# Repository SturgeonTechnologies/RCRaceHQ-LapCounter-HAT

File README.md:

# RC Race HQ Lap Counter HAT

Open hardware for the [RC Race HQ](https://www.rcracehq.com) lap counter: a
Raspberry Pi 4 HAT that sits between the track's timing loop and the RTL-SDR.

| Path | What | Status |
|---|---|---|
| [`burst-detector-hat/`](burst-detector-hat) | v0: splitter + AD8307 log detector + LM393 burst flag + ADS1115 signal strength. KiCad project, gerbers, JLCPCB BOM/CPL | Fab files done, board not built or tested yet |
| [`breadboard-v1.md`](breadboard-v1.md) | v1 loop front end (LMH6624 amp + detector) as a breadboard build: parts checklist, ASCII schematic, hole-by-hole steps | Not built or tested yet |

Transponder IDs come from the RTL-SDR through
[OpenStint](https://github.com/zsellera/openstint). The HAT tells the Pi
*when* a transponder is over the loop and how strong it is. Without a HAT, the
loop coax goes straight into the RTL-SDR, which is how the lap counter runs
today.

Software and Pi setup:
[RCRaceHQ-LapCounter-Install](https://github.com/SturgeonTechnologies/RCRaceHQ-LapCounter-Install)
and [RCRaceHQ-LapCounter-App](https://github.com/SturgeonTechnologies/RCRaceHQ-LapCounter-App).

## Buy or build

Anyone may build this board. Assembled, tested boards will be available from
RC Race HQ.

## License

[CERN-OHL-S-2.0](LICENSE). You may build, modify and sell boards made from
this design. If you ship a modified board, you must publish your modified
design files under the same licence. See [NOTICE](NOTICE). "RC Race HQ" is a
trademark of Sturgeon Technologies LLC and isn't covered by the licence.

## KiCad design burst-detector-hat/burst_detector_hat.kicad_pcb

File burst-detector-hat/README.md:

# Burst-detector HAT (lap counter v0 front end)

Raspberry Pi 4 HAT (65 × 56.5 mm, M2.5 holes on the HAT pattern) that sits
between the timing loop and the RTL-SDR.

```
loop -> balun -> J1 SMA -> TVS -> 3-way resistive splitter -+-> J2 SMA -> RTL-SDR (IDs, via OpenStint)
                                                           +-> 3-8 MHz bandpass -> AD8307 log detector
AD8307 RSSI (25 mV/dB) -+-> ADS1115 AIN0 (I2C 0x48, pins 3/5) -> signal strength
                        +-> LM393 vs RV1 threshold -> GPIO17 (pin 11) + BURST LED
```

It tells the Pi *when* a transponder is over the loop and how strong it is.
The ID still comes from the SDR. Power is the Pi's 5 V/3.3 V header pins, so
USB-C or a PoE HAT both work. J4 is an unconnected pass-through for the Pi's
2×2 PoE header, with a copper keep-out around it.

## Ordering (JLCPCB)
- Gerbers: `fab/burst_detector_hat_gerbers.zip` (2 layers, 1.6 mm, HASL).
- Assembly (top side): `fab/bom_jlcpcb.csv` + `fab/cpl_jlcpcb.csv`.
  Check every LCSC part number and the U1/U2/U3 pin-1 rotation in JLC's preview.
- Hand-solder: J3 2×20 stacking header, J4 2×2 stacking header (optional).

## Bring-up
1. Power from the Pi; LED off with no loop connected.
2. `i2cdetect -y 1` shows `48`.
3. Turn RV1 until the LED goes out with the loop empty, then back off a little.
4. Transponder on the loop: LED on, ~650 rising edges/s on GPIO17.

## Rebuild
`source ~/tools/kicad-env.sh && JAVA=... FREEROUTING=... tools/build.sh`
regenerates everything from `tools/design.py`, autoroutes, runs ERC/DRC
(`fab/reports/`) and rewrites `fab/`.

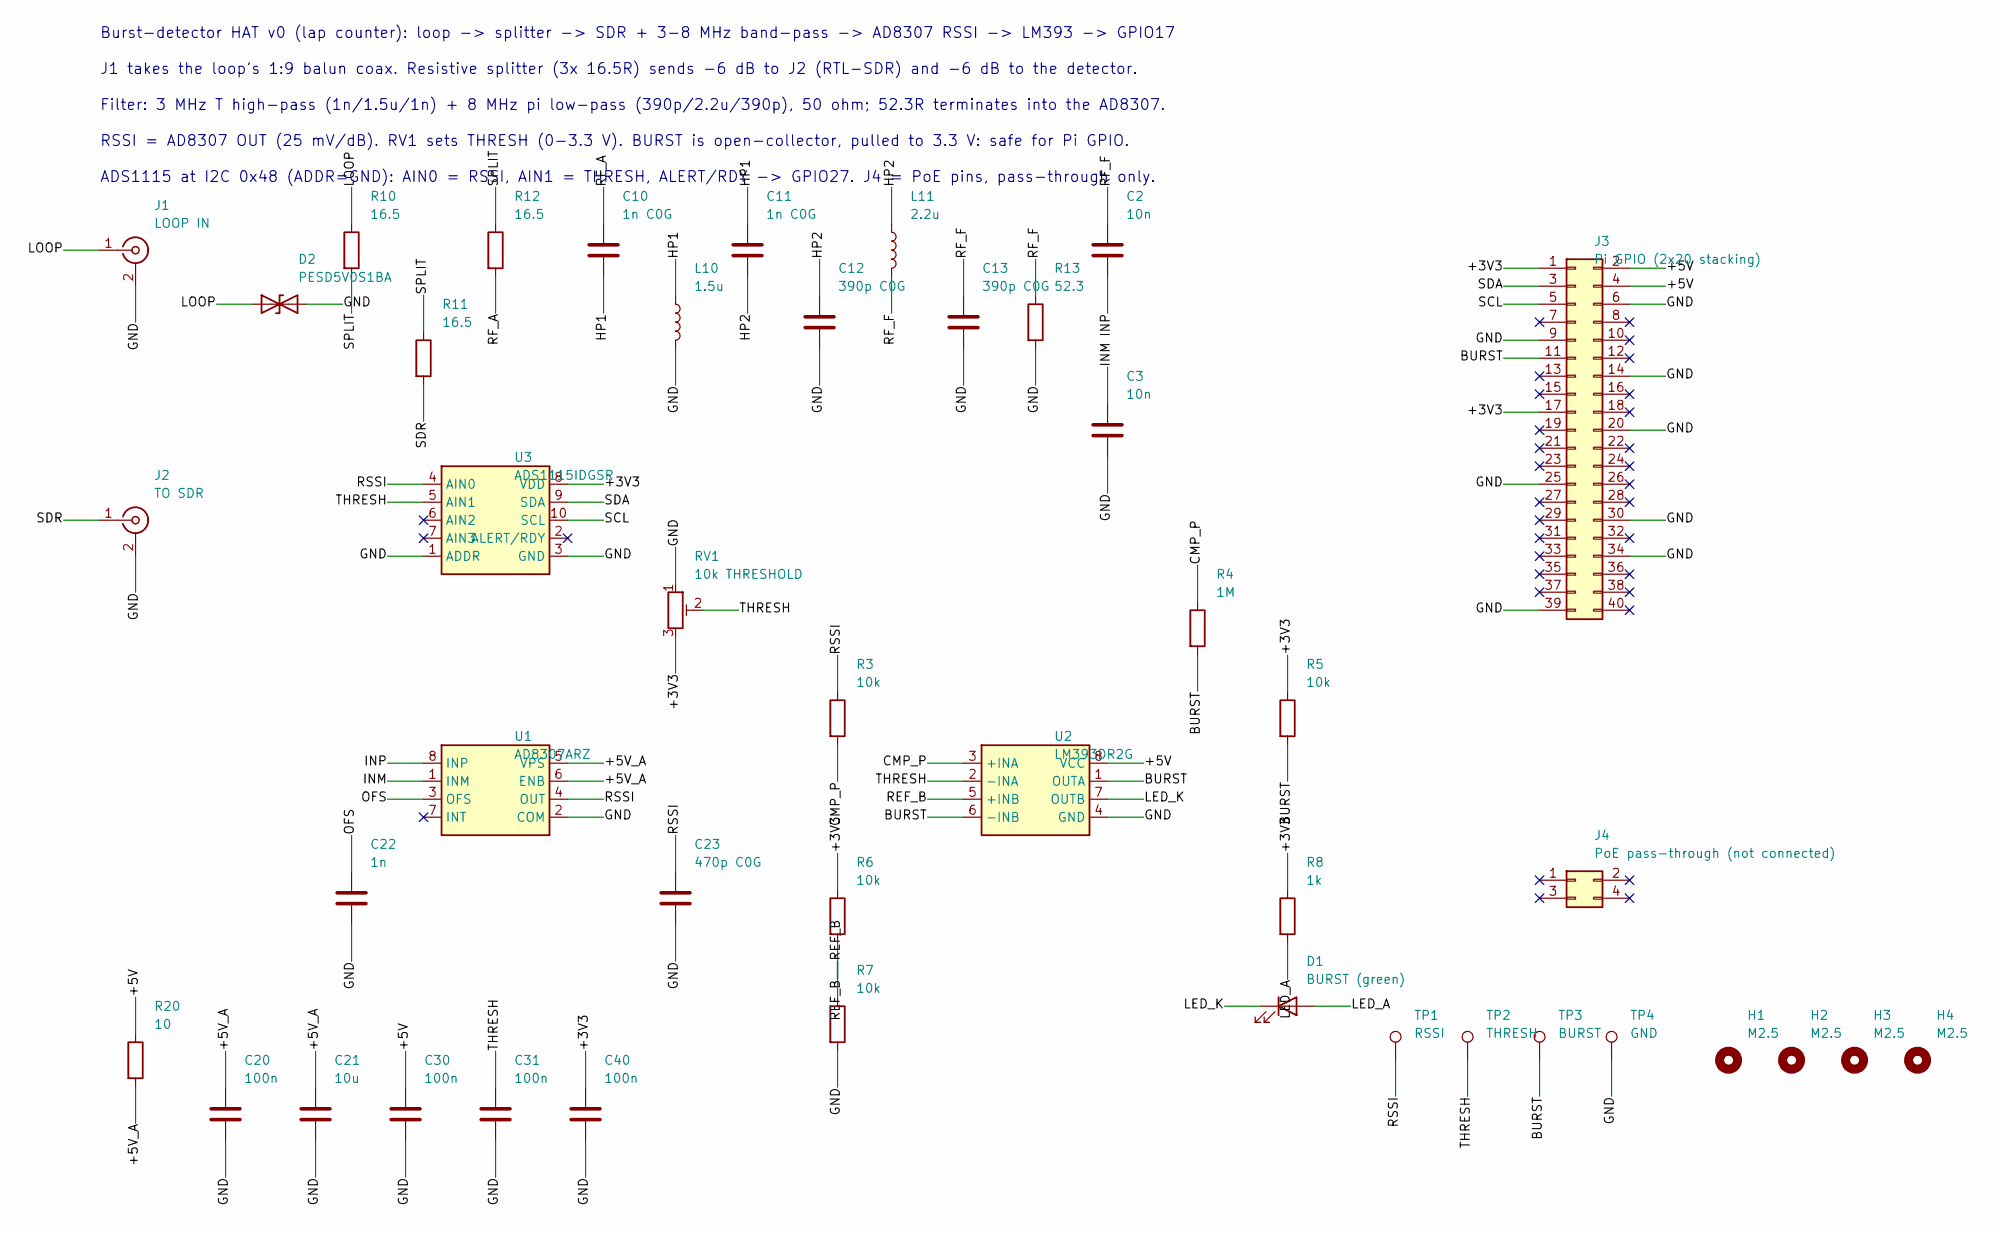
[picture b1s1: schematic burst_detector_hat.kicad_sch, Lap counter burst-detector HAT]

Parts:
C2, C3: 10n; C_0603_1608Metric; LCSC C1589
C10, C11: 1n C0G; C_0603_1608Metric; LCSC C1636
C12, C13: 390p C0G; C_0603_1608Metric; LCSC C1667
C20, C30, C31, C40: 100n; C_0603_1608Metric; LCSC C1591
C21: 10u; C_0805_2012Metric; LCSC C15850
C22: 1n; C_0603_1608Metric; LCSC C1636
C23: 470p C0G; C_0603_1608Metric; LCSC C36252
D1: BURST (green); LED_0603_1608Metric; LCSC C12624
D2: PESD5V0S1BA; D_SOD-323; LCSC C19224
H1, H2, H3, H4: M2.5; MountingHole_2.7mm_M2.5
J1: LOOP IN; SMA_Amphenol_132289_EdgeMount; LCSC C3172723
J2: TO SDR; SMA_Amphenol_132289_EdgeMount; LCSC C3172723
J3: Pi GPIO (2x20 stacking); PinHeader_2x20_P2.54mm_Vertical
J4: PoE pass-through (not connected); PinHeader_2x02_P2.54mm_Vertical
L10: 1.5u; L_1206_3216Metric; LCSC C2885920
L11: 2.2u; L_1206_3216Metric; LCSC C1048
R3, R5, R6, R7: 10k; R_0603_1608Metric; LCSC C25804
R4: 1M; R_0603_1608Metric; LCSC C22935
R8: 1k; R_0603_1608Metric; LCSC C21190
R10, R11, R12: 16.5; R_0603_1608Metric; LCSC C12054
R13: 52.3; R_0603_1608Metric; LCSC C81321
R20: 10; R_0603_1608Metric; LCSC C22859
RV1: 10k THRESHOLD; Potentiometer_Bourns_TC33X_Vertical; LCSC C719176
TP1: RSSI; TestPoint_Pad_D1.5mm
TP2: THRESH; TestPoint_Pad_D1.5mm
TP3: BURST; TestPoint_Pad_D1.5mm
TP4: GND; TestPoint_Pad_D1.5mm
U1: AD8307ARZ; SOIC-8_3.9x4.9mm_P1.27mm; LCSC C495272
U2: LM393DR2G; SOIC-8_3.9x4.9mm_P1.27mm; LCSC C7955
U3: ADS1115IDGSR; MSOP-10_3x3mm_P0.5mm; LCSC C37593

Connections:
+3V3: C40.1, J3.1, J3.17, R5.1, R6.1, R8.1, RV1.3, U3.8 (VDD)
+5V: C30.1, J3.2, J3.4, R20.1, U2.8 (VCC)
+5V_A: C20.1, C21.1, R20.2, U1.5 (VPS), U1.6 (ENB)
BURST: J3.11, R4.2, R5.2, TP3.1, U2.1 (OUTA), U2.6 (-INB)
CMP_P: R3.2, R4.1, U2.3 (+INA)
GND: C3.2, C12.2, C13.2, C20.2, C21.2, C22.2, C23.2, C30.2, C31.2, C40.2, D2.2 (A2), J1.2 (Ext), J2.2 (Ext), J3.6, J3.9, J3.14, J3.20, J3.25, J3.30, J3.34, J3.39, L10.2, R7.2, R13.2, RV1.1, TP4.1, U1.2 (COM), U2.4 (GND), U3.1 (ADDR), U3.3 (GND)
HP1: C10.2, C11.1, L10.1
HP2: C11.2, C12.1, L11.1
INM: C3.1, U1.1 (INM)
INP: C2.2, U1.8 (INP)
LED_A: D1.2 (A), R8.2
LED_K: D1.1 (K), U2.7 (OUTB)
LOOP: D2.1 (A1), J1.1 (In), R10.1
OFS: C22.1, U1.3 (OFS)
REF_B: R6.2, R7.1, U2.5 (+INB)
RF_A: C10.1, R12.2
RF_F: C2.1, C13.1, L11.2, R13.1
RSSI: C23.1, R3.1, TP1.1, U1.4 (OUT), U3.4 (AIN0)
SCL: J3.5, U3.10 (SCL)
SDA: J3.3, U3.9 (SDA)
SDR: J2.1 (In), R11.2
SPLIT: R10.2, R11.1, R12.1
THRESH: C31.1, RV1.2, TP2.1, U2.2 (-INA), U3.5 (AIN1)

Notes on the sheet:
Burst-detector HAT v0 (lap counter): loop -> splitter -> SDR + 3-8 MHz band-pass -> AD8307 RSSI -> LM393 -> GPIO17
J1 takes the loop's 1:9 balun coax. Resistive splitter (3x 16.5R) sends -6 dB to J2 (RTL-SDR) and -6 dB to the detector.
Filter: 3 MHz T high-pass (1n/1.5u/1n) + 8 MHz pi low-pass (390p/2.2u/390p), 50 ohm; 52.3R terminates into the AD8307.
RSSI = AD8307 OUT (25 mV/dB). RV1 sets THRESH (0-3.3 V). BURST is open-collector, pulled to 3.3 V: safe for Pi GPIO.
ADS1115 at I2C 0x48 (ADDR=GND): AIN0 = RSSI, AIN1 = THRESH, ALERT/RDY -> GPIO27. J4 = PoE pins, pass-through only.

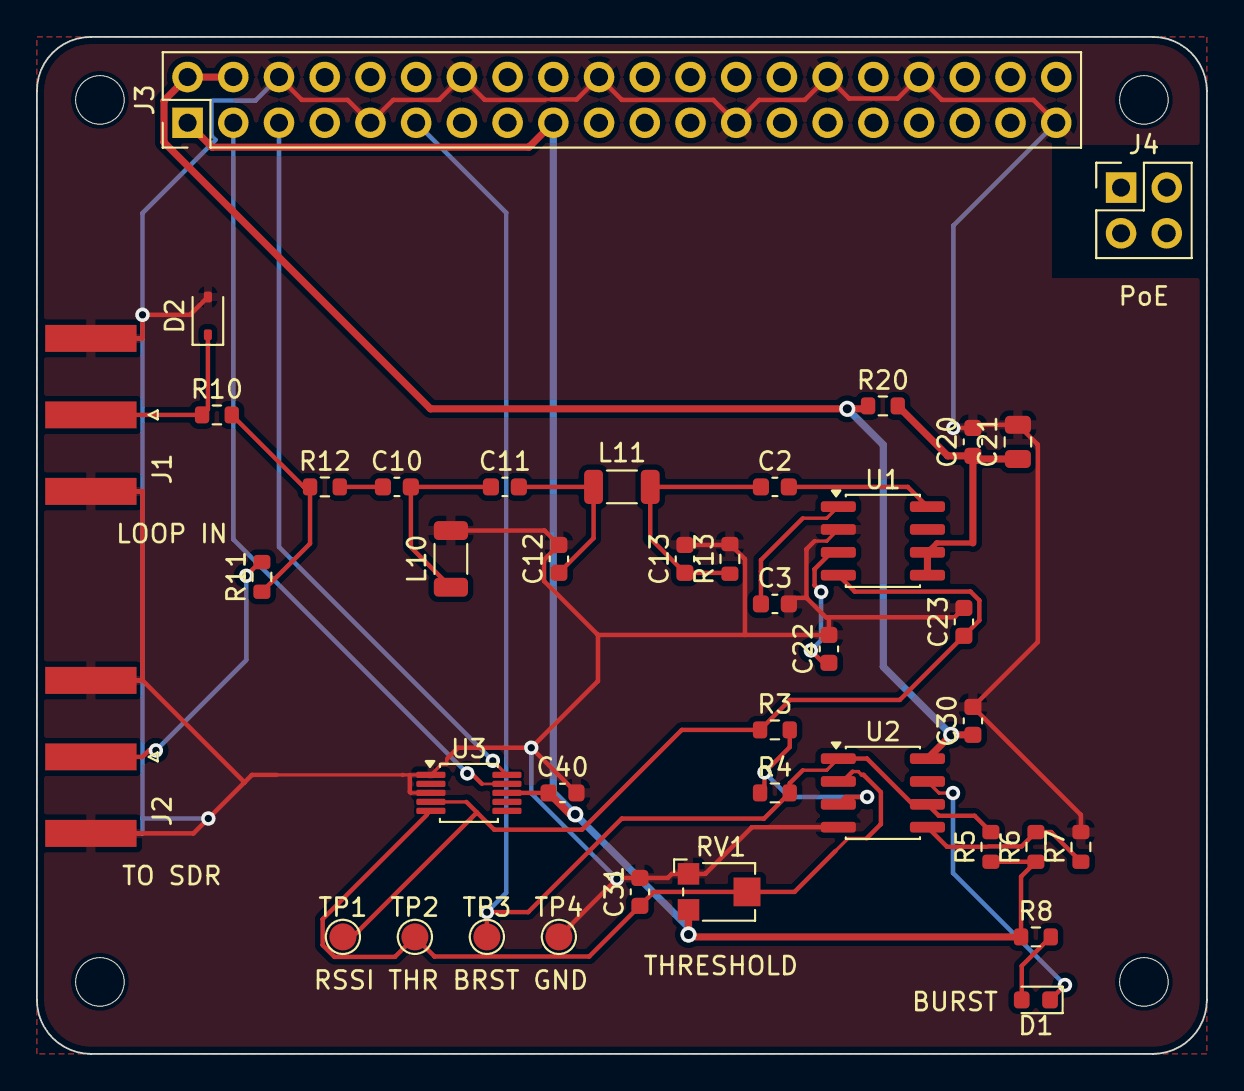
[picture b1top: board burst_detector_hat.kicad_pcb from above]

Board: 2 copper layers, 65.0 x 56.5 mm, 44 parts (0 on the bottom side), 23 nets.

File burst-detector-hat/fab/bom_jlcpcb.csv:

Comment,Designator,Footprint,LCSC Part #
LOOP IN,J1,SMA_Amphenol_132289_EdgeMount,C3172723
TO SDR,J2,SMA_Amphenol_132289_EdgeMount,C3172723
PESD5V0S1BA,D2,D_SOD-323,C19224
16.5,"R10,R11,R12",R_0603_1608Metric,C12054
1n C0G,"C10,C11",C_0603_1608Metric,C1636
1.5u,L10,L_1206_3216Metric,C2885920
390p C0G,"C12,C13",C_0603_1608Metric,C1667
2.2u,L11,L_1206_3216Metric,C1048
52.3,R13,R_0603_1608Metric,C81321
10n,"C2,C3",C_0603_1608Metric,C1589
AD8307ARZ,U1,SOIC-8_3.9x4.9mm_P1.27mm,C495272
10,R20,R_0603_1608Metric,C22859
100n,"C20,C30,C31,C40",C_0603_1608Metric,C1591
10u,C21,C_0805_2012Metric,C15850
1n,C22,C_0603_1608Metric,C1636
470p C0G,C23,C_0603_1608Metric,C36252
LM393DR2G,U2,SOIC-8_3.9x4.9mm_P1.27mm,C7955
10k,"R3,R5,R6,R7",R_0603_1608Metric,C25804
1M,R4,R_0603_1608Metric,C22935
1k,R8,R_0603_1608Metric,C21190
BURST (green),D1,LED_0603_1608Metric,C12624
10k THRESHOLD,RV1,Potentiometer_Bourns_TC33X_Vertical,C719176
ADS1115IDGSR,U3,MSOP-10_3x3mm_P0.5mm,C37593

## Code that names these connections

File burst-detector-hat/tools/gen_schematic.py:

"""Generate burst_detector_hat.kicad_sch from design.py.

Every connected pin gets a short wire stub ending in a net label, so the
schematic reads as a net list rather than a wiring diagram. Unused pins get a
no-connect flag so ERC stays clean.
"""
import os
import pathlib
import re
import uuid

from design import NETS, NO_CONNECT, PARTS, PROJECT

HERE = pathlib.Path(__file__).resolve().parent.parent
SYMDIR = pathlib.Path(os.environ.get("KICAD9_SYMBOL_DIR", "/usr/share/kicad/symbols"))
ROOT = str(uuid.uuid5(uuid.NAMESPACE_URL, "sturgeon/burst-detector-hat/root"))


def uid(*parts):
    # Stable UUIDs keep regenerated files diff-friendly.
    return str(uuid.uuid5(uuid.NAMESPACE_URL, "sturgeon/burst-detector-hat/" + "/".join(parts)))


# ------------------------------------------------------- tiny s-expr parser --

TOKEN = re.compile(r'\(|\)|"(?:[^"\\]|\\.)*"|[^\s()]+')


def parse(text):
    stack, cur = [], []
    for m in TOKEN.finditer(text):
        t = m.group(0)
        if t == "(":
            stack.append(cur)
            cur = []
        elif t == ")":
            done, cur = cur, stack.pop()
            cur.append(done)
        else:
            cur.append(t)
    return cur[0]


def dump(node, indent=0):
    if not isinstance(node, list):
        return node
    pad = "  " * indent
    simple = all(not isinstance(c, list) for c in node)
    if simple:
        return "(" + " ".join(node) + ")"
    parts = [c for c in node if not isinstance(c, list)]
    kids = [c for c in node if isinstance(c, list)]
    s = "(" + " ".join(parts)
    for k in kids:
        s += "\n" + pad + "  " + dump(k, indent + 1)
    return s + ")"


def find(node, key):
    return [c for c in node if isinstance(c, list) and c and c[0] == key]


def unq(s):
    return s[1:-1] if s.startswith('"') else s


_libs = {}


def lib_symbol(lib_id):
    lib, name = lib_id.split(":")
    if lib not in _libs:
        path = HERE / f"{lib}.kicad_sym" if lib == PROJECT else SYMDIR / f"{lib}.kicad_sym"
        _libs[lib] = {unq(s[1]): s for s in find(parse(path.read_text()), "symbol")}
    sym = [list(x) if isinstance(x, list) else x for x in _libs[lib][name]]
    if find(sym, "extends"):
        raise SystemExit(f"{lib_id} uses extends; pick a base symbol")
    sym[1] = f'"{lib_id}"'
    return sym


def pins_of(sym):
    """{number: (x, y, angle)} in symbol coordinates (y up)."""
    out = {}

    def walk(n):
        for c in n:
            if isinstance(c, list):
                if c and c[0] == "pin":
                    at = find(c, "at")[0]
                    num = unq(find(c, "number")[0][1])
                    out[num] = (float(at[1]), float(at[2]), int(float(at[3])))
                else:
                    walk(c)
    walk(sym)
    return out


# ---------------------------------------------------------------- emitters --

def prop(name, value, x, y, hide=False, justify=None):
    h = " (hide yes)" if hide else ""
    j = f" (justify {justify})" if justify else ""
    return (f'    (property "{name}" "{value}" (at {x:.2f} {y:.2f} 0)\n'
            f'      (effects (font (size 1.27 1.27)){j}{h}))\n')


def symbol_instance(ref, part, pins):
    x, y = part["sch"]
    s = [f'  (symbol (lib_id "{part["sym"]}") (at {x:.2f} {y:.2f} 0) (unit 1)\n'
         f'    (exclude_from_sim no) (in_bom yes) (on_board yes) (dnp no)\n'
         f'    (uuid "{uid("sym", ref)}")\n']
    top = max([p[1] for p in pins.values()] + [2.54])
    s.append(prop("Reference", ref, x + 2.54, y - top - 3.81, justify="left"))
    s.append(prop("Value", part["value"], x + 2.54, y - top - 1.27, justify="left"))
    s.append(prop("Footprint", part["fp"], x, y, hide=True))
    s.append(prop("Datasheet", "", x, y, hide=True))
    if part.get("lcsc"):
        s.append(prop("LCSC", part["lcsc"], x, y, hide=True))
    for num in sorted(pins):
        s.append(f'    (pin "{num}" (uuid "{uid("pin", ref, num)}"))\n')
    s.append(f'    (instances (project "{PROJECT}" (path "/{ROOT}" '
             f'(reference "{ref}") (unit 1))))\n  )\n')
    return "".join(s)


def main():
    pad_net = {(r, p): n for n, members in NETS.items() for r, p in members}
    nc = set(NO_CONNECT)
    lib_syms, body = {}, []

    for ref, part in PARTS.items():
        sym = lib_symbol(part["sym"])
        lib_syms[part["sym"]] = sym
        pins = pins_of(sym)
        body.append(symbol_instance(ref, part, pins))
        sx, sy = part["sch"]
        for num, (px, py, ang) in pins.items():
            x, y = sx + px, sy - py               # schematic y points down
            if (ref, num) in nc:
                body.append(f'  (no_connect (at {x:.2f} {y:.2f}) (uuid "{uid("nc", ref, num)}"))\n')
                continue
            net = pad_net.get((ref, num))
            if net is None:
                raise SystemExit(f"{ref}.{num} is neither on a net nor marked no-connect")
            # Stub runs away from the body: opposite to the pin's direction.
            dx, dy = {0: (-1, 0), 90: (0, 1), 180: (1, 0), 270: (0, -1)}[ang]
            ex, ey = x + dx * 5.08, y + dy * 5.08
            body.append(f'  (wire (pts (xy {x:.2f} {y:.2f}) (xy {ex:.2f} {ey:.2f}))\n'
                        f'    (stroke (width 0) (type default)) (uuid "{uid("w", ref, num)}"))\n')
            angle, just = {(-1, 0): (180, "right"), (1, 0): (0, "left"),
                           (0, -1): (90, "left"), (0, 1): (270, "right")}[(dx, dy)]
            body.append(f'  (label "{net}" (at {ex:.2f} {ey:.2f} {angle})\n'
                        f'    (effects (font (size 1.27 1.27)) (justify {just}))\n'
                        f'    (uuid "{uid("lbl", ref, num)}"))\n')

    notes = [
        (20.32, 20.32, "Burst-detector HAT v0 (lap counter): loop -> splitter -> SDR + 3-8 MHz band-pass -> AD8307 RSSI -> LM393 -> GPIO17"),
        (20.32, 25.4, "J1 takes the loop's 1:9 balun coax. Resistive splitter (3x 16.5R) sends -6 dB to J2 (RTL-SDR) and -6 dB to the detector."),
        (20.32, 30.48, "Filter: 3 MHz T high-pass (1n/1.5u/1n) + 8 MHz pi low-pass (390p/2.2u/390p), 50 ohm; 52.3R terminates into the AD8307."),
        (20.32, 35.56, "RSSI = AD8307 OUT (25 mV/dB). RV1 sets THRESH (0-3.3 V). BURST is open-collector, pulled to 3.3 V: safe for Pi GPIO."),
        (20.32, 40.64, "ADS1115 at I2C 0x48 (ADDR=GND): AIN0 = RSSI, AIN1 = THRESH, ALERT/RDY -> GPIO27. J4 = PoE pins, pass-through only."),
    ]
    for i, (x, y, t) in enumerate(notes):
        body.append(f'  (text "{t}" (exclude_from_sim no) (at {x:.2f} {y:.2f} 0)\n'
                    f'    (effects (font (size 1.524 1.524)) (justify left))\n'
                    f'    (uuid "{uid("note", str(i))}"))\n')

    libs = "\n".join("    " + dump(s, 2) for s in lib_syms.values())
    out = (f'(kicad_sch (version 20250114) (generator "eeschema") (generator_version "9.0")\n'
           f'  (uuid "{ROOT}")\n  (paper "A4")\n'
           f'  (title_block (title "Lap counter burst-detector HAT") (rev "1.0") '
           f'(company "Sturgeon Technologies") (comment 1 "Generated by tools/gen_schematic.py"))\n'
           f'  (lib_symbols\n{libs}\n  )\n'
           + "".join(body) +
           '  (sheet_instances (path "/" (page "1")))\n  (embedded_fonts no)\n)\n')
    (HERE / f"{PROJECT}.kicad_sch").write_text(out)
    print("schematic written")


if __name__ == "__main__":
    main()
